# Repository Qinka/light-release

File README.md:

Photon
===========================

Photom is a bluetooth-based shutter release and has some RGB LEDs for light painting. Based on ESP32-WROVER-E and written in Rust.

------------

LED bar prototype V2 (with APA102)

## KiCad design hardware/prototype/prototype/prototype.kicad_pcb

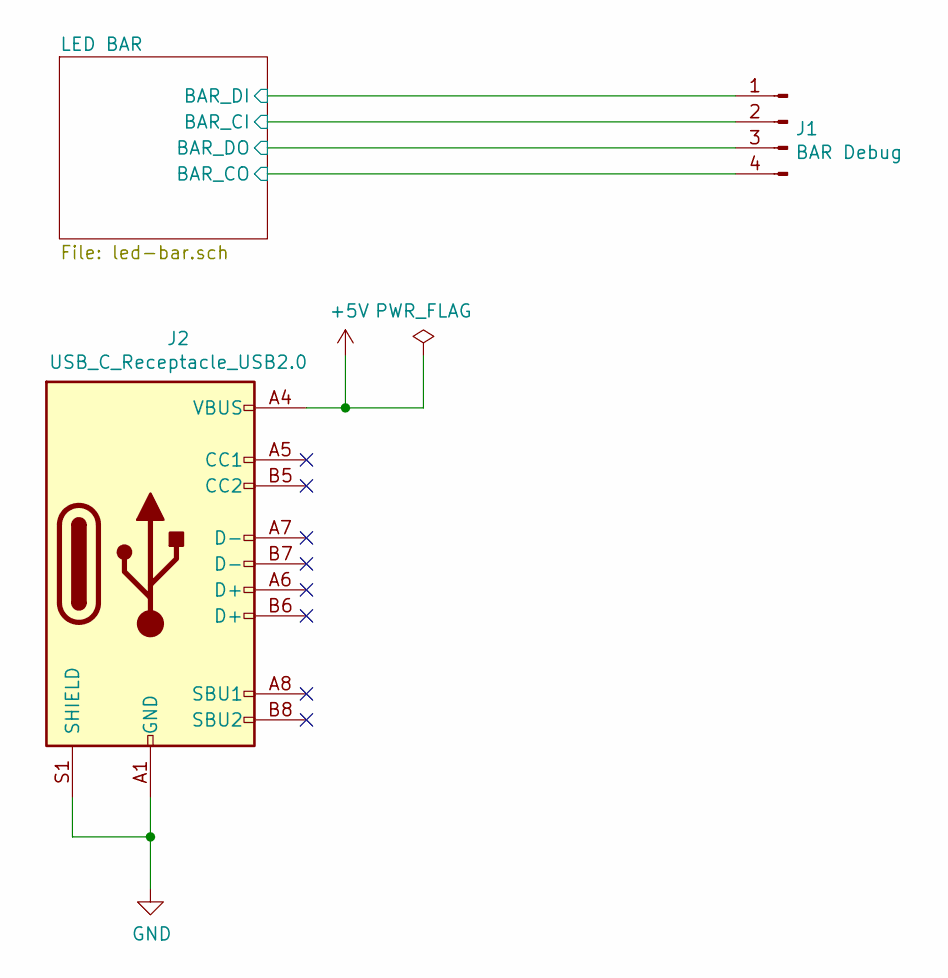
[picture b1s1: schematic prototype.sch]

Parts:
J1: BAR Debug; PinHeader_1x04_P2.54mm_Horizontal
J2: USB_C_Receptacle_USB2.0; USB_C_Receptacle_HRO_TYPE-C-31-M-12

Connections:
+5V: J2.A4 (VBUS), J2.A9 (VBUS), J2.B4 (VBUS), J2.B9 (VBUS); also elsewhere on the board
/LED BAR/BAR_CI: J1.2; also elsewhere on the board
/LED BAR/BAR_CO: J1.4; also elsewhere on the board
/LED BAR/BAR_DI: J1.1; also elsewhere on the board
/LED BAR/BAR_DO: J1.3; also elsewhere on the board
GND: J2.A1 (GND), J2.A12 (GND), J2.B1 (GND), J2.B12 (GND), J2.S1 (SHIELD); also elsewhere on the board

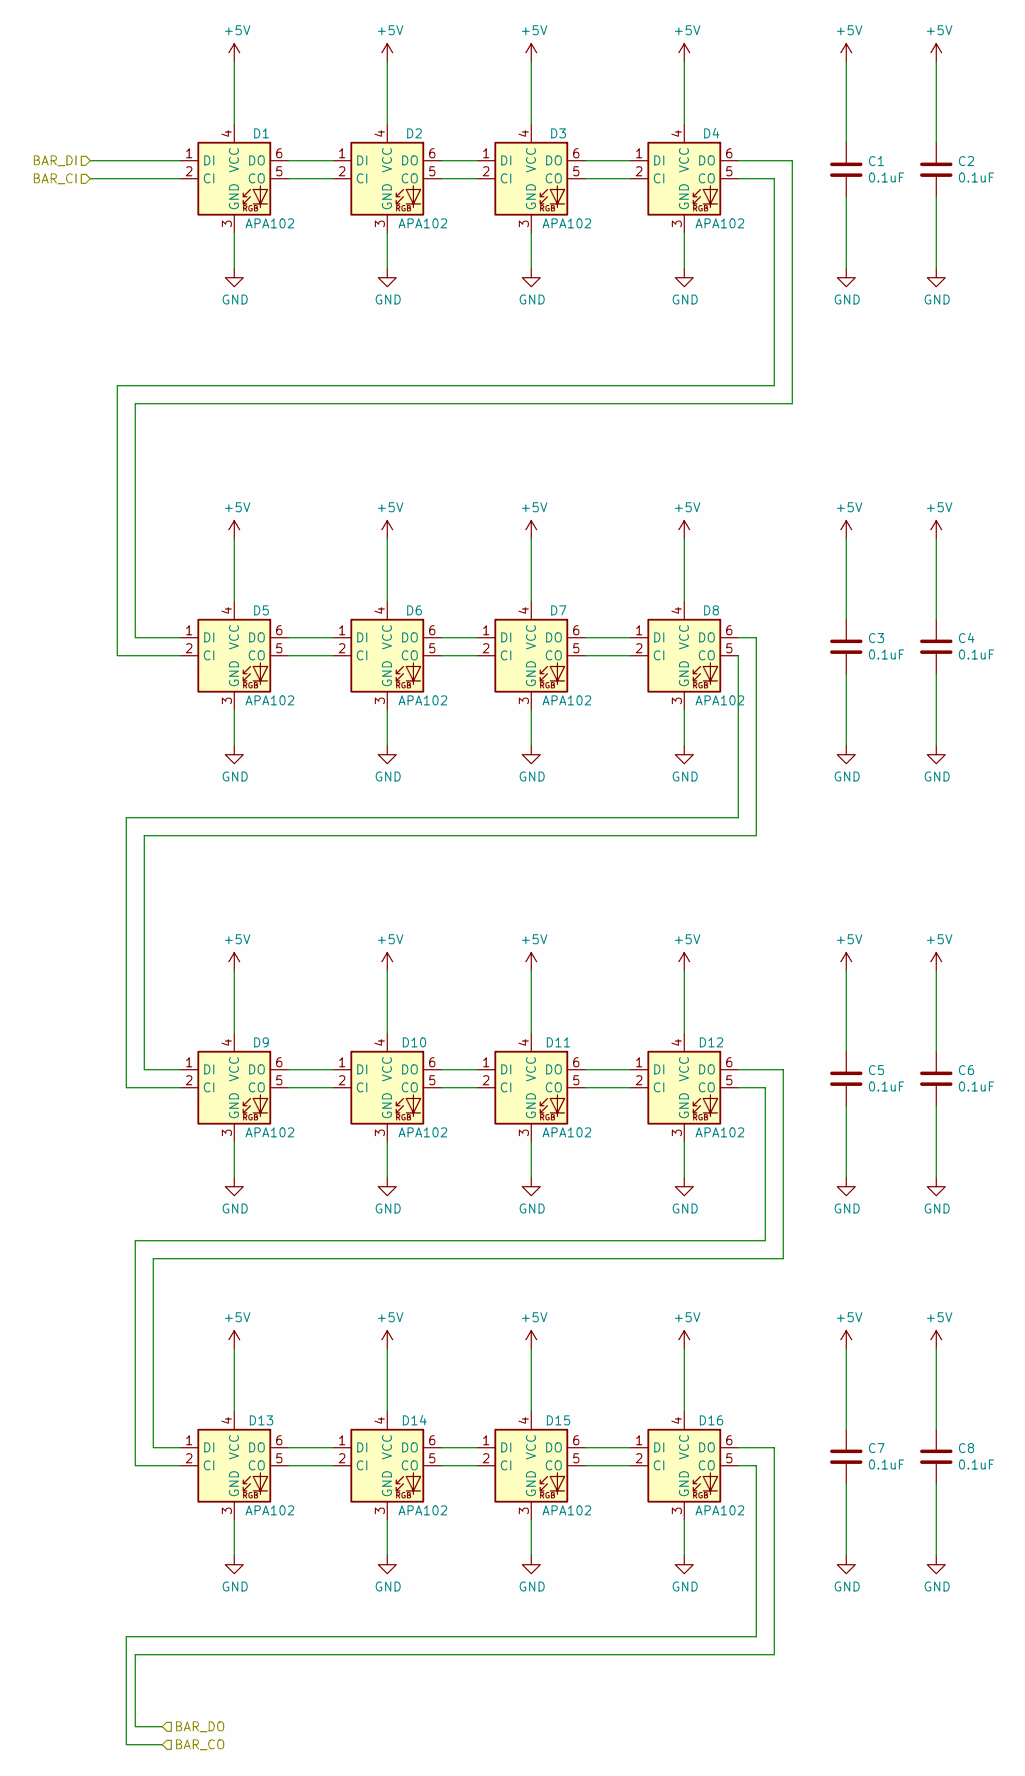
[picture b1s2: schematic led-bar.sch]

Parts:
C1, C2, C3, C4, C5, C6, C7, C8: 0.1uF; C_0603_1608Metric
D1, D2, D3, D4, D5, D6, D7, D8, D9, D10, D11, D12, D13, D14, D15, D16: APA102; LED_RGB_5050-6

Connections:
+5V: C1.1, C2.1, C3.1, C4.1, C5.1, C6.1, C7.1, C8.1, D1.4 (VCC), D2.4 (VCC), D3.4 (VCC), D4.4 (VCC), D5.4 (VCC), D6.4 (VCC), D7.4 (VCC), D8.4 (VCC), D9.4 (VCC), D10.4 (VCC), D11.4 (VCC), D12.4 (VCC), D13.4 (VCC), D14.4 (VCC), D15.4 (VCC), D16.4 (VCC); also elsewhere on the board
/LED BAR/BAR_CI: D1.2 (CI); also elsewhere on the board
/LED BAR/BAR_CO: D16.5 (CO); also elsewhere on the board
/LED BAR/BAR_DI: D1.1 (DI); also elsewhere on the board
/LED BAR/BAR_DO: D16.6 (DO); also elsewhere on the board
GND: C1.2, C2.2, C3.2, C4.2, C5.2, C6.2, C7.2, C8.2, D1.3 (GND), D2.3 (GND), D3.3 (GND), D4.3 (GND), D5.3 (GND), D6.3 (GND), D7.3 (GND), D8.3 (GND), D9.3 (GND), D10.3 (GND), D11.3 (GND), D12.3 (GND), D13.3 (GND), D14.3 (GND), D15.3 (GND), D16.3 (GND); also elsewhere on the board
unnamed: D1.5 (CO), D2.2 (CI)
unnamed: D1.6 (DO), D2.1 (DI)
unnamed: D2.5 (CO), D3.2 (CI)
unnamed: D2.6 (DO), D3.1 (DI)
unnamed: D3.5 (CO), D4.2 (CI)
unnamed: D3.6 (DO), D4.1 (DI)
unnamed: D4.5 (CO), D5.2 (CI)
unnamed: D4.6 (DO), D5.1 (DI)
unnamed: D5.5 (CO), D6.2 (CI)
unnamed: D5.6 (DO), D6.1 (DI)
unnamed: D6.5 (CO), D7.2 (CI)
unnamed: D6.6 (DO), D7.1 (DI)
unnamed: D7.5 (CO), D8.2 (CI)
unnamed: D7.6 (DO), D8.1 (DI)
unnamed: D8.5 (CO), D9.2 (CI)
unnamed: D8.6 (DO), D9.1 (DI)
unnamed: D9.6 (DO), D10.1 (DI)
unnamed: D9.5 (CO), D10.2 (CI)
unnamed: D10.5 (CO), D11.2 (CI)
unnamed: D10.6 (DO), D11.1 (DI)
unnamed: D11.5 (CO), D12.2 (CI)
unnamed: D11.6 (DO), D12.1 (DI)
unnamed: D12.5 (CO), D13.2 (CI)
unnamed: D12.6 (DO), D13.1 (DI)
unnamed: D13.5 (CO), D14.2 (CI)
unnamed: D13.6 (DO), D14.1 (DI)
unnamed: D14.5 (CO), D15.2 (CI)
unnamed: D14.6 (DO), D15.1 (DI)
unnamed: D15.5 (CO), D16.2 (CI)
unnamed: D15.6 (DO), D16.1 (DI)

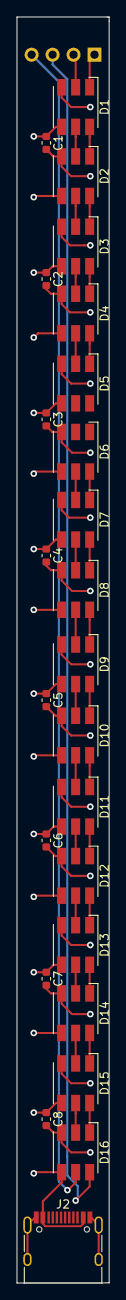
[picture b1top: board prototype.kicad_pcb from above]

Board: 2 copper layers, 11.2 x 153.5 mm, 26 parts (1 on the bottom side), 36 nets.

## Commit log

2021-02-14 Initial update
2021-03-14 Update proto bar
